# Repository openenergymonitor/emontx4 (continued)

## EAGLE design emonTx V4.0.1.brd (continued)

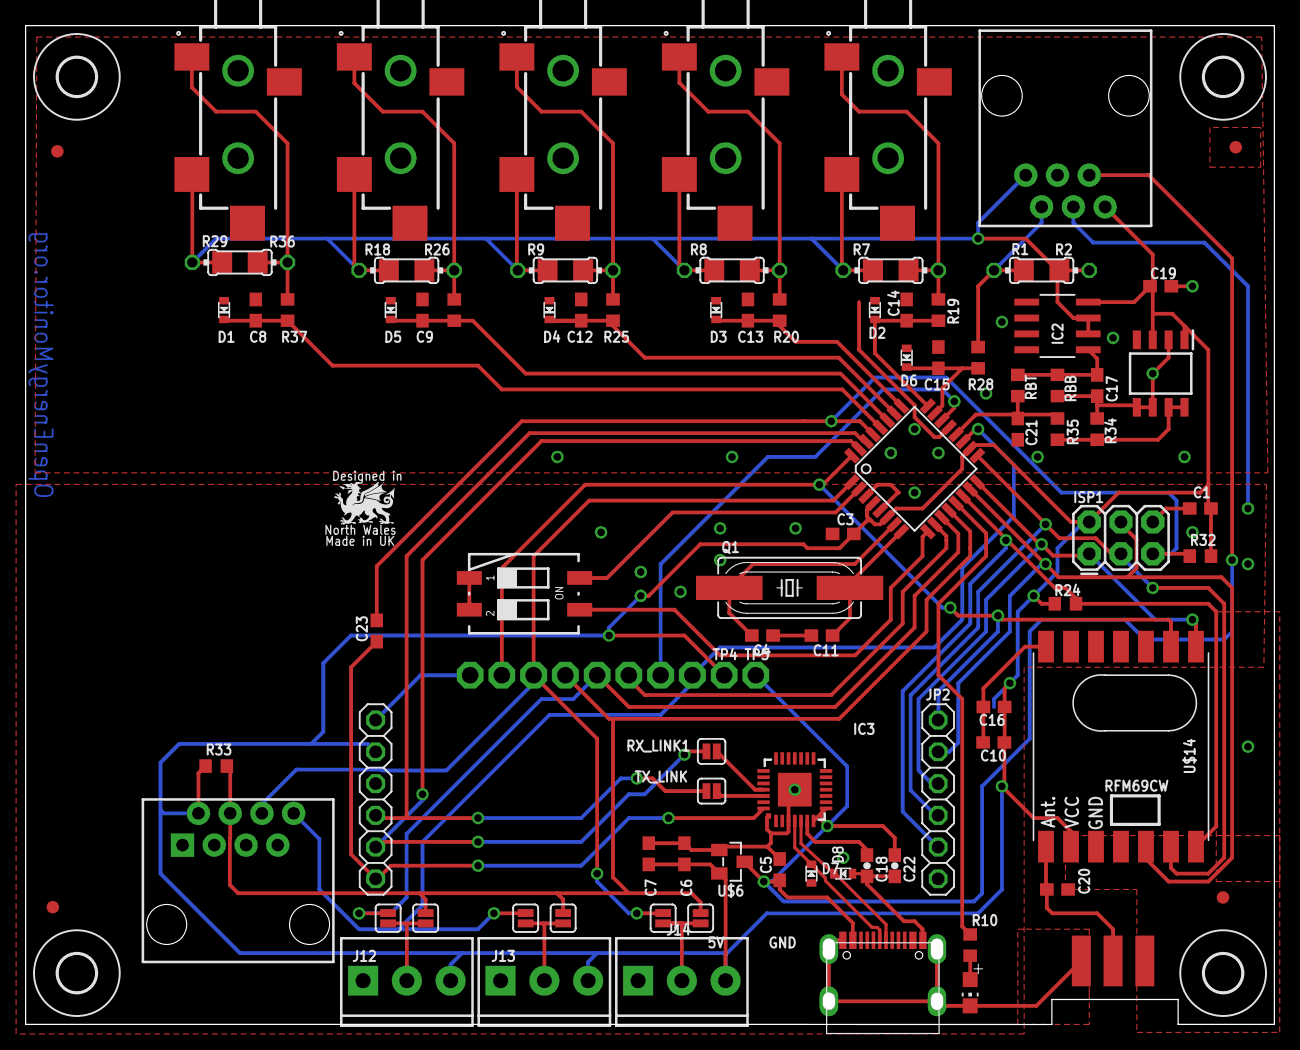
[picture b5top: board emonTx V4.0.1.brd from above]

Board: 2 copper layers, 99.9 x 79.9 mm, 107 parts (1 on the bottom side), 50 nets.

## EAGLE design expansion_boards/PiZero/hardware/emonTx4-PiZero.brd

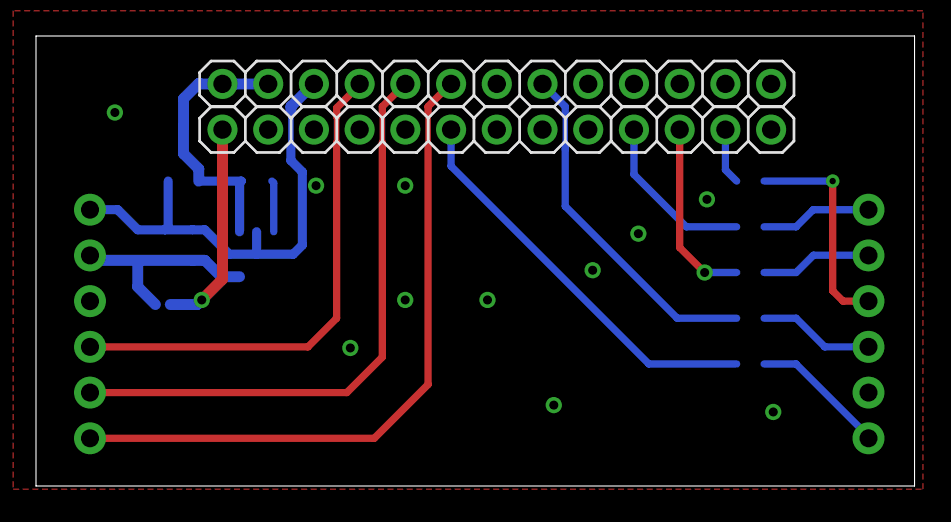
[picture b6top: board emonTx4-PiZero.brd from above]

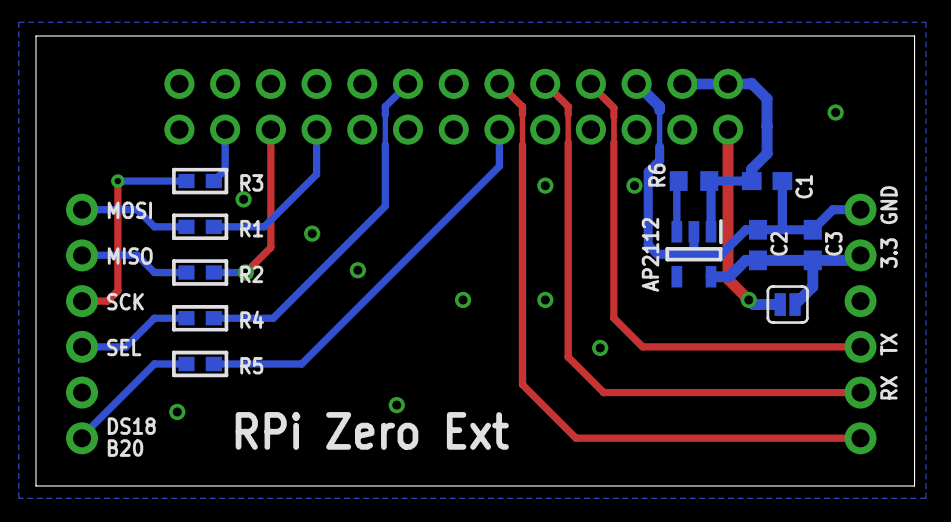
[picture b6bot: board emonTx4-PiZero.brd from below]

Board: 2 copper layers, 48.8 x 25.0 mm, 15 parts (11 on the bottom side), 18 nets.

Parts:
3.3V_LINK: SOLDERJUMPERNC; SJ_2S
AP2112: AP2112K-3.3TRG1; SOT95P282X130-5N
C1, C2: 1uF 6V; C0603
C3: 100nF; C0603
JP1, JP2: FTDI; 1X06_ROUND_70
JP5, JP6: 1X13-BIG
R1, R2, R3, R4, R5: 1k; _0603
R6: 10K; R0603

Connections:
3.3V: 3.3V_LINK.1, AP2112.5, C2.2, C3.2, JP1.5
+5V: AP2112.1, C1.2, JP5.1, JP5.2, R6.1
AVR_RX: JP1.3, JP5.4
AVR_TX: JP1.2, JP5.5
DS18B20: JP2.1, R5.2
GND: AP2112.2, C1.1, C2.1, C3.1, JP1.6, JP5.3, JP5.7, JP5.10, JP6.5
unnamed: JP5.8, R4.2
unnamed: JP6.6, R5.1
unnamed: 3.3V_LINK.2, JP6.1
unnamed: JP6.10, R1.1
unnamed: JP6.11, R2.1
unnamed: JP6.12, R3.1
unnamed: AP2112.3, R6.2
RFM_MISO: JP2.5, R2.2
RFM_MOSI: JP2.6, R1.2
RFM_SCK: JP2.4, R3.2
RFM_SEL: JP2.3, R4.1
_RESET: JP1.1, JP5.6

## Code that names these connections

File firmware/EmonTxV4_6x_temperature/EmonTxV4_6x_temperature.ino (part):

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                                                           // For safety, thus MUST default to false. (Required due to faulty ESP8266 software.)

//----------------------------emonTx V4 hard-wired connections-----------------------------------
const byte LEDpin      = PIN_PB2;  // emonTx V4 LED
const byte DIP_switch1 = PIN_PA4;  // RF node ID (default no change in node ID, switch on for nodeID + 1) switch off D8 is HIGH from internal pullup
const byte DIP_switch2 = PIN_PA5;  // Voltage selection 240 / 120 V AC (default switch off 240V)  - switch off D9 is HIGH from internal pullup

//---------------------------------CT availability status----------------------------------------
byte CT_count = 0;
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    
    // Frequency is currently hardcoded to 433Mhz in library
    #if RadioFormat == RFM69_LOW_POWER_LABS
    rf.setPins(PIN_PB5,PIN_PC0,PIN_PC1,PIN_PC2);
    #endif
    rf.initialize(RF69_433MHZ, EEProm.nodeID, EEProm.networkGroup); 
    rf.encrypt("89txbe4p8aik5kt3"); // ignored if jeelib classic
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  EmonLibCM_setAssumedVrms(EEProm.assumedVrms);

  EmonLibCM_setPulseEnable(EEProm.pulse_enable);                       // Enable pulse counting
  EmonLibCM_setPulsePin(PIN_PA6);
  EmonLibCM_setPulseMinPeriod(EEProm.pulse_period);

  EmonLibCM_setTemperatureDataPin(PIN_PB4);                            // OneWire data pin (emonTx V4)
  EmonLibCM_setTemperaturePowerPin(PIN_PB3);                           // Temperature sensor Power Pin - 19 for emonTx V4  (-1 = Not used. No sensors, or sensor are permanently powered.)
  EmonLibCM_setTemperatureResolution(11);                              // Resolution in bits, allowed values 9 - 12. 11-bit resolution, reads to 0.125 degC
  EmonLibCM_setTemperatureAddresses(EEProm.allAddresses);              // Name of array of temperature sensors
  EmonLibCM_setTemperatureArray(allTemps);                             // Name of array to receive temperature measurements
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        Serial.print(F(",I6:")); Serial.print(EmonLibCM_getIrms(EmonLibCM_getLogicalChannel(6)),3);
        
        Serial.print(F(",pf1:")); Serial.print(EmonLibCM_getPF(EmonLibCM_getLogicalChannel(1)),4);
        Serial.print(F(",pf2:")); Serial.print(EmonLibCM_getPF(EmonLibCM_getLogicalChannel(2)),4);
        Serial.print(F(",pf3:")); Serial.print(EmonLibCM_getPF(EmonLibCM_getLogicalChannel(3)),4);
        Serial.print(F(",pf4:")); Serial.print(EmonLibCM_getPF(EmonLibCM_getLogicalChannel(4)),4);
        Serial.print(F(",pf5:")); Serial.print(EmonLibCM_getPF(EmonLibCM_getLogicalChannel(5)),4);
        Serial.print(F(",pf6:")); Serial.println(EmonLibCM_getPF(EmonLibCM_getLogicalChannel(6)),4);
        delay(80);
      }
    }
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
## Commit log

2022-05-09 emontx4 v4.0.2-beta
2022-05-09 images
2022-05-09 update image
2022-05-09 fascia
2022-05-30 v4.0.3
2022-06-15 minor fascia revisions
2022-06-16 v4.0.4
2022-06-27 add pdf and images
2022-06-28 add gerbers
2022-07-06 update fascia
2022-07-07 Firmware
2022-07-08 rfm69 native firmware
2022-07-13 firmware images
2022-07-14 first attempt at compiling using pio
2022-08-07 Fix Typo
    Frimware -> Firmware
2022-10-05 fix online configuration, update default CT calibration
2022-10-05 v4.0.5 routes 5V to uart connector
2022-10-05 updated gitignore
2022-10-05 extension board hardware files
2022-10-05 pipico ext image
2022-10-05 pipico example software
2022-10-05 basic esp32 arduino examples
2022-10-05 update hex file
2022-10-06 ESP8266 basic client example
2022-10-17 Add JSON Output to sketch
    Add an option to switch a JSON Format Serial data output on/off
2022-10-17 Enabled the EProm loading
2022-10-20 pi pico emoncms client example with AES128CBC encryption
2022-10-20 esp8266 emoncms client with AES128CBC encryption
2022-10-20 esp32 emoncms client example with AES128CBC encryption
2022-10-23 updated pi pico extension design
2022-10-23 ignore .pio folder
2022-10-23 example combining serial configuration with aes encryption example
2022-10-23 minor change to serial config
2022-10-23 read full config line and validate length
2022-10-23 serial config example
2022-10-24 usa cal removed, removal of white space seperated output
2022-10-24 return assumed vrms if no voltage sensor
2022-10-24 web config tool image
2022-10-25 Error in the JSOn Output
2022-10-25 updated lastest EmonTxV4CM_rfm69n hex file
2022-10-26 change ct calibration, led stays on until msg 0
2022-10-26 update version and change log
2022-10-26 factory test
2022-10-26 remove .hex from repo, now in github releases
2022-10-26 minor serial print typo, remove factory RF test
2022-10-26 ESP8266 emoncms client AES128CBC plus serial config
2022-10-26 ESP8266 huzzah adapter board
2022-10-26 ESP32 client with encryption and serialconfig
2022-10-26 example with display
2022-10-26 pi pico LED feedback
2022-10-31 fix URL
2022-11-03 install guide p1
2022-11-15 Create single EmonTxV4 Firmware with option to switch between radio formats
2022-11-15 update defines
2022-11-15 default lowpowerlabs
2022-11-15 jeelib library changes
2022-11-15 radio library api consistency
2022-11-17 improve radioFormat naming
2022-11-18 compiled firmware
2022-11-21 calibrate reference voltage at startup
2022-11-21 json format option thanks to Brian Orpin
2022-11-21 update compiled firmware
2022-11-22 updated guide
2022-11-23 comment on EEWL
2022-11-23 example installs
2022-11-23 update quick guide
2022-11-24 move to docs
2022-11-24 documentation moved to docs
2022-11-25 docs tweaks
2022-11-25 start on expansion board documentation and rename extension to expansion board
2022-11-25 software links
2022-11-25 adding an emontx4 to an existing installation
2022-11-25 page on voltage sensors
2022-11-25 resize images
2022-11-26 v1.5.0
2022-11-26 acacconverter picture, voltage sensor page improvements
2022-11-26 nodeid 17, swap DIP nodeid, zero all 6 Energy values
2022-11-26 updated hex
2022-11-28 fix eeprom eewl overlap
2022-11-29 firmware 1.5.3, sightly slower sample rate, temperature sensors disabled if not detected at startup
2022-11-29 a couple more decimal places
2022-11-29 documentation tree
2022-11-30 start on technical guide
2022-11-30 minor correction
2022-11-30 technical guide pictures
2022-11-30 fix MHz
2022-11-30 emonhub configuration note
2022-12-02 updated ESP8266 adapter board
2022-12-02 esp8266 details
2022-12-02 fix emonsd password and use note,tip etc
2022-12-02 add links
2022-12-02 install guide changes
2022-12-03 start on temperature, pulse and analog page, accuracy and tech spec in overview
2022-12-03 more detail on temperature sensing
2022-12-04 analog input section
2022-12-04 pulse counting and rj45 pinout
2022-12-16 Fix node ID in example emonhub config
2022-12-19 emontx4 firmware v1.5.4 fix eeprom overlap properly
2022-12-19 firmware image
2022-12-19 note that system update may be required
2022-12-26 emontx4 heat pump monitor firmware example
2022-12-26 updated to match 1.5.4
2022-12-26 heat pump monitor documentation first draft
2022-12-26 voltage sensing technical
2022-12-27 move picture to the top
2022-12-27 ltspice simulation
2022-12-28 documentation improvements
2022-12-28 fix node decoder
2022-12-28 fix typo
2022-12-28 github_url
2023-01-25 update links
2023-03-09 V1.2 fascia
2023-03-17 fix typos
2023-03-30 Add notes regarding serial config
2023-04-17 update emontx4 firmware
2023-04-19 6x DS18B20 temperature sensor example
2023-04-19 use dxcore onewire
2023-04-19 use onewire_isr_fix branch
2023-04-25 update version
2023-04-25 update 6x temperature sensor example
2023-04-26 Fix disabling of temperature sensing at startup if none detected
2023-04-26 v1.5.7: Fix disabling of temperature sensing at startup if none detected
2023-04-26 update platformio
2023-04-26 update versions
2023-04-26 only attempt to print temperature sensor address and check for sensors if enabled
2023-04-26 update emontx4 heatpump firmware example
2023-05-07 EmonTx4 emonLibDB 3-phase 6CT firmware example with serial config and EEPROM
2023-05-08 rename db firmware
2023-05-08 update firmware documentation
2023-05-08 precompiled binary
2023-05-09 change default nodeid in new EmonTxV4_DB_3phase_6CT firmware
2023-05-15 12 CT fascia
2023-05-16 v2.0.1 re-configure CT phase order
2023-05-17 change default phase arrangement
2023-05-17 compiled 3-phase v2.0.2
2023-06-07 emonTx4 v4.0.5 BOM
2023-06-20 firmware.md: Remove : from "How to compile and upload firmware"
    Make TOC more consistent on https://docs.openenergymonitor.org/emontx4/index.html
2023-06-22 add platformio compile and upload instructions
2023-07-03 start on 6ct documentation
2023-07-03 update index
2023-07-03 expansion board documentation
2023-07-03 update exp docs
2023-07-03 update docs
2023-07-03 firmware guide
2023-07-03 docs update
2023-07-03 doc update
2023-07-13 Update firmware.md
    Fix typo in PlatformIO link.
2023-07-21 fix lib versions
2023-07-24 auto reconnect basic esp8266 example
2023-07-25 simple client post example
2023-07-25 update do use char array, append esp_wifi msg and connect count
2023-07-31 Add "3PH" to three-phase serial print statup
2023-08-14 12CT WiFi ext firmware example
2023-08-18 Update overview.md
    Add "buy in shop" link.
2023-09-15 Fix node decoder for EmonTxV4_6x_temperature
2023-09-29 post Irms via serial
2023-09-29 print Irms key values
2023-11-08 send Irms via RF
2024-02-23 serial print 6x temp to identify
2024-04-17 updated 12 CT serial firmware
2024-04-18 rename serial firmware and add to docs
2024-05-14 move firmware to common avrdb_firmware repository
2024-05-14 update firmware descriptions
2024-05-14 update guides
2024-05-14 update configuration
2024-05-14 update technical
2024-05-14 update overview
2024-05-15 update temperature section
2024-05-15 update analog read docs
2024-05-15 update heatpump monitor docs
2024-05-15 update expansion boards page
2024-05-15 updated 6ct expansion board page
2024-05-16 update pulse documentation
2024-05-20 node decoder examples
2024-05-23 update firmware page
2024-05-26 shorten headings
2024-05-26 3-phase 4-wire and n,american systems
2024-06-15 6ct_expansion_board.md: Clarify firmware guide for older vs newer
2025-10-13 readme.md: Update link to docs.openenergymonitor.org
2025-10-13 overview.md: emonTx5 is definitely released now
    Reorganized text for clarity and improved flow.
